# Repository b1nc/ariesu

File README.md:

# ariesu アリエス

Ariesu keyboard PCB and plate files.
A 45%ish ergo-keyboard.
Warning: This keyboard has an extremely weird layout.

----

The prototypes are in perfectly working condition.

There will not be a group-buy, however, all the PCB and case files are open-source
so feel free to order the parts yourself!

The PCB is the main part of this project, it's nothing fancy but it's something I'm
proud of. :^) (No backlits, sorry.)

Since the case files are stacked acrylic, it features a 0 degree typing angle, but
feel free to make a case for the PCB if you want something unique.

## Features (Very simple PCB) 
* Mini-B USB connection. (Yes, I know.)

* 51 keys.

* ATmega32U4

* MX-only no per key leds.

* No backlit leds.

## Thanks to
- ai03 for his PCB guide and hadi for his in-depth explanations.

- Izzy7k for sticking up with my bs and staying up with me.

- hadi's Youtube channel: https://www.youtube.com/channel/UCpWGAJr2AU7LPUwVYbBQZRg

- ai03's PCB guide: https://wiki.ai03.com/books/pcb-design/

## Addtional Items
I purchased most of the screws and standoffs from McMaster-Carr. Here are the parts
if you are going to use the stacked acrylic case in this project.

- Standoffs: Zinc-Plated Brass Female Threaded Hex Standoff 4.5mm Hex, 19mm Long, M3 x 0.5mm Thread (https://www.mcmaster.com/92080A014/)

- Screws: Brass Pan Head Slotted Screws M3 x 0.5mm Thread, 6mm Long (https://www.mcmaster.com/90928A301/)

- Bumpons: Adhesive-Back Bumpers Polyurethane, 1/2" Long, 1" Wide, 1/8" High, Durometer 65A, Black (https://www.mcmaster.com/95495K861/)

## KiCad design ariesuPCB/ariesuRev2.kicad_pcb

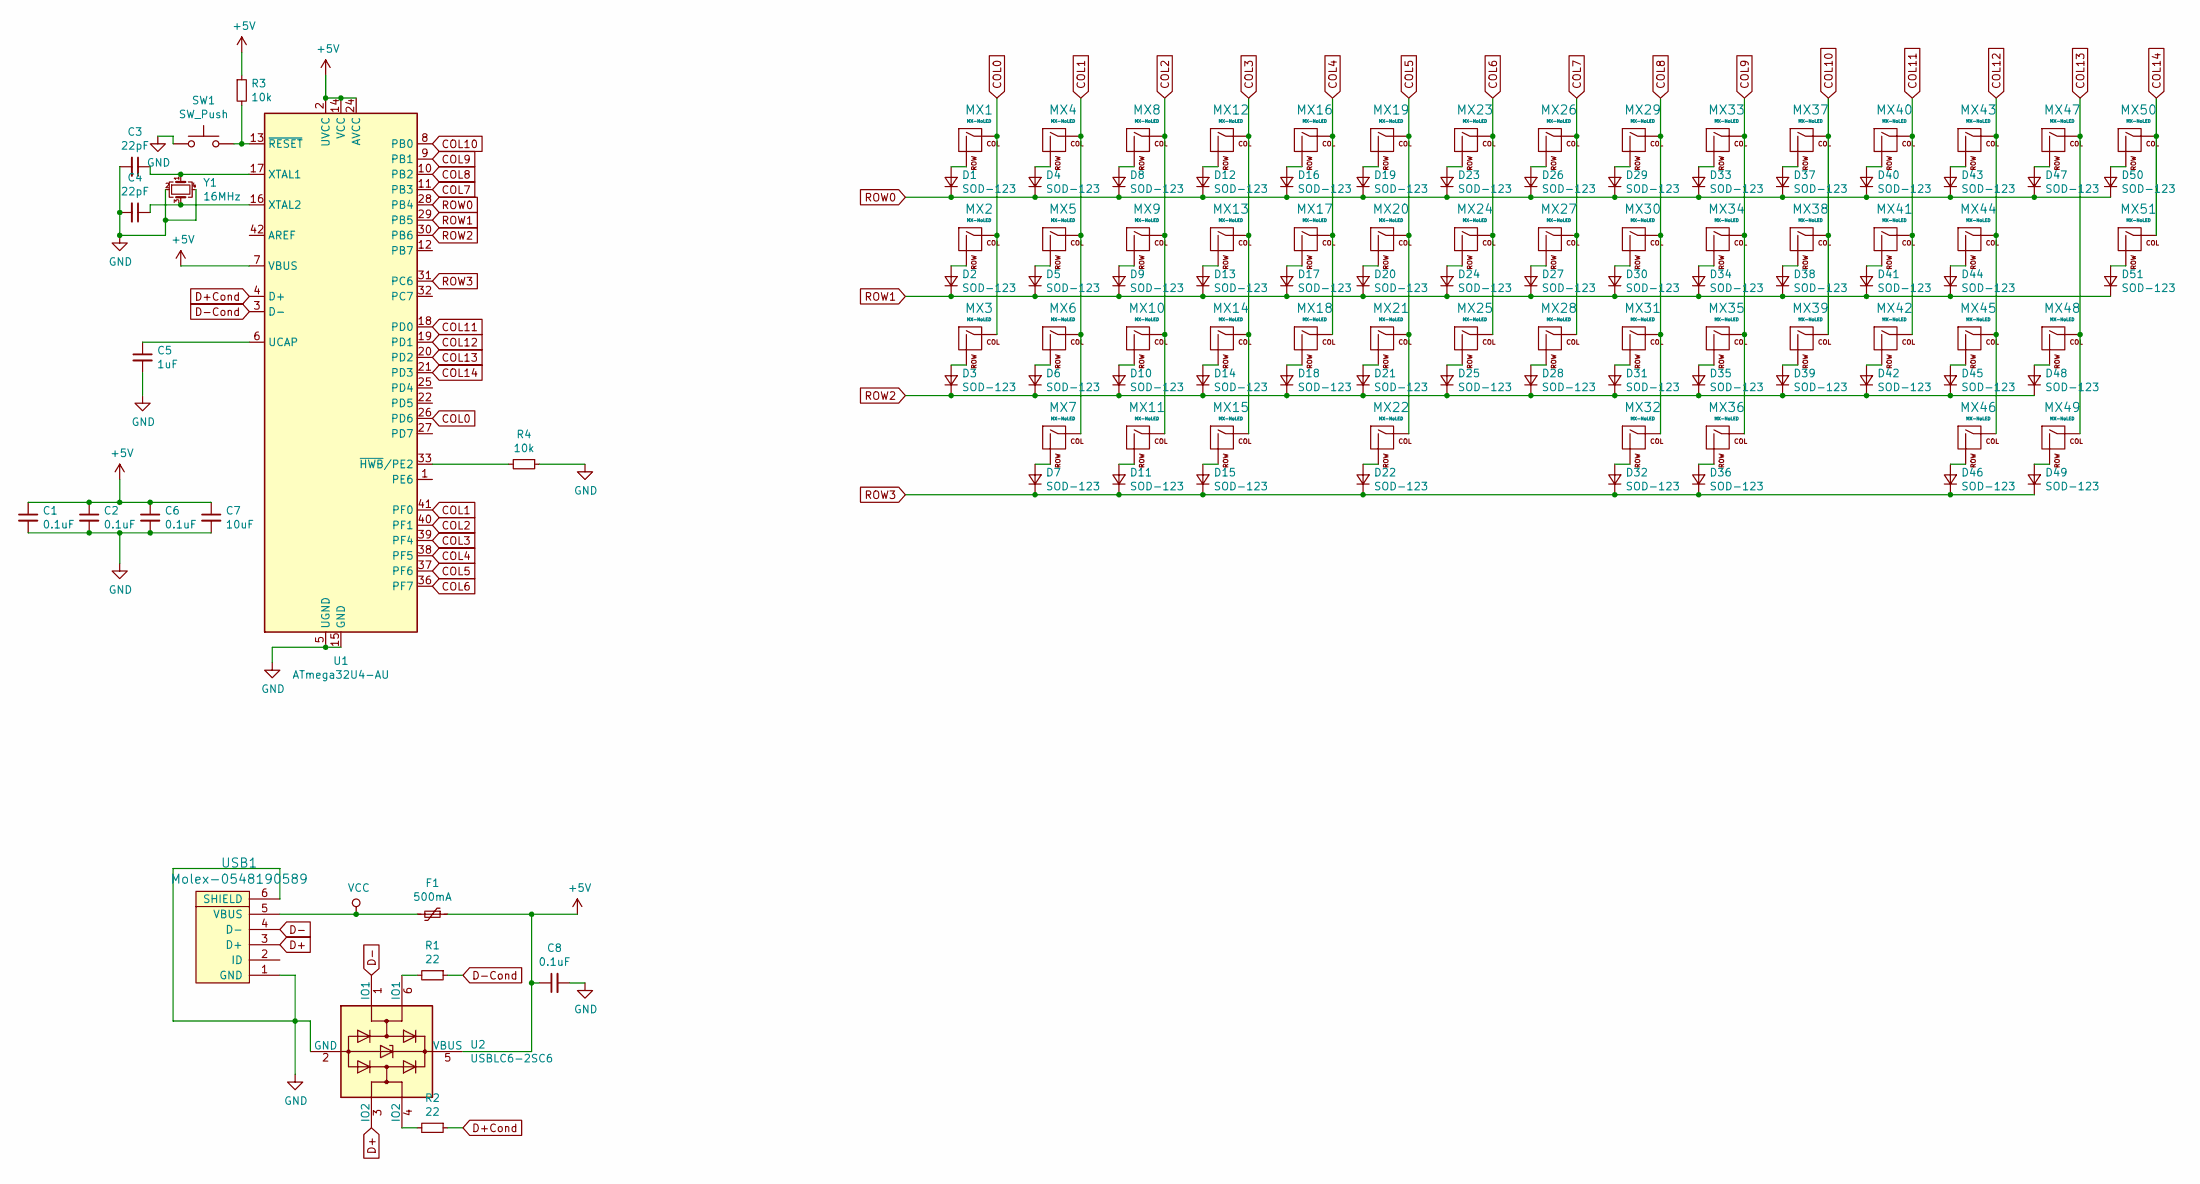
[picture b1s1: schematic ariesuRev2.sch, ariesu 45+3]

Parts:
C1, C2, C6, C8: 0.1uF; C_0805_2012Metric
C3, C4: 22pF; C_0805_2012Metric
C5: 1uF; C_0805_2012Metric
C7: 10uF; C_0805_2012Metric
D1, D2, D3, D4, D5, D6, D7, D8, D9, D10, D11, D12, D13, D14, D15, D16, D17, D18, D19, D20, D21, D22, D23, D24, D25, D26, D27, D28, D29, D30, D31, D32, D33, D34, D35, D36, D37, D38, D39, D40, D41, D42, D43, D44, D45, D46, D47, D48, D49, D50, D51: SOD-123; D_SOD-123
F1: 500mA; Fuse_1206_3216Metric
MX1, MX2, MX3, MX4, MX5, MX6, MX7, MX8, MX9, MX10, MX11, MX12, MX13, MX14, MX15, MX16, MX17, MX18, MX19, MX20, MX21, MX23, MX24, MX25, MX26, MX27, MX28, MX29, MX30, MX31, MX33, MX34, MX35, MX36, MX37, MX38, MX39, MX40, MX41, MX42, MX43, MX44, MX45, MX46, MX47, MX48, MX49, MX50, MX51: MX-NoLED; MXOnly-1U-NoLED
MX22, MX32: MX-NoLED; MXOnly-2.25U-ReversedStabilizers-NoLED
R1, R2: 22; R_0805_2012Metric
R3, R4: 10k; R_0805_2012Metric
SW1: SW_Push; SKQG-1155865
U1: ATmega32U4-AU; TQFP-44_10x10mm_P0.8mm
U2: USBLC6-2SC6; SOT-23-6
USB1: Molex-0548190589
Y1: 16MHz; Crystal_SMD_3225-4Pin_3.2x2.5mm

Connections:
+5V: C1.1, C2.1, C6.1, C7.1, C8.1, F1.1, R3.1, U1.2 (UVCC), U1.7 (VBUS), U1.14 (VCC), U1.24 (AVCC), U1.34 (VCC), U1.44 (AVCC), U2.5 (VBUS)
COL0: MX1.1 (COL), MX2.1 (COL), MX3.1 (COL), U1.26 (PD6)
COL1: MX4.1 (COL), MX5.1 (COL), MX6.1 (COL), MX7.1 (COL), U1.41 (PF0)
COL2: MX8.1 (COL), MX9.1 (COL), MX10.1 (COL), MX11.1 (COL), U1.40 (PF1)
COL3: MX12.1 (COL), MX13.1 (COL), MX14.1 (COL), MX15.1 (COL), U1.39 (PF4)
COL4: MX16.1 (COL), MX17.1 (COL), MX18.1 (COL), U1.38 (PF5)
COL5: MX19.1 (COL), MX20.1 (COL), MX21.1 (COL), MX22.1 (COL), U1.37 (PF6)
COL6: MX23.1 (COL), MX24.1 (COL), MX25.1 (COL), U1.36 (PF7)
COL7: MX26.1 (COL), MX27.1 (COL), MX28.1 (COL), U1.11 (PB3)
COL8: MX29.1 (COL), MX30.1 (COL), MX31.1 (COL), MX32.1 (COL), U1.10 (PB2)
COL9: MX33.1 (COL), MX34.1 (COL), MX35.1 (COL), MX36.1 (COL), U1.9 (PB1)
COL10: MX37.1 (COL), MX38.1 (COL), MX39.1 (COL), U1.8 (PB0)
COL11: MX40.1 (COL), MX41.1 (COL), MX42.1 (COL), U1.18 (PD0)
COL12: MX43.1 (COL), MX44.1 (COL), MX45.1 (COL), MX46.1 (COL), U1.19 (PD1)
COL13: MX47.1 (COL), MX48.1 (COL), MX49.1 (COL), U1.20 (PD2)
COL14: MX50.1 (COL), MX51.1 (COL), U1.21 (PD3)
D+: U2.3 (IO2), USB1.3 (D+)
D+Cond: R2.1, U1.4 (D+)
D-: U2.1 (IO1), USB1.4 (D-)
D-Cond: R1.1, U1.3 (D-)
GND: C1.2, C2.2, C3.2, C4.2, C5.2, C6.2, C7.2, C8.2, R4.1, SW1.1, U1.5 (UGND), U1.15 (GND), U1.23 (GND), U1.35 (GND), U1.43 (GND), U2.2 (GND), USB1.1 (GND), USB1.6 (SHIELD), Y1.2, Y1.4
unnamed: C3.1, U1.17 (XTAL1), Y1.1
unnamed: C4.1, U1.16 (XTAL2), Y1.3
unnamed: C5.1, U1.6 (UCAP)
unnamed: D1.2 (A), MX1.2 (ROW)
unnamed: D2.2 (A), MX2.2 (ROW)
unnamed: D3.2 (A), MX3.2 (ROW)
unnamed: D4.2 (A), MX4.2 (ROW)
unnamed: D5.2 (A), MX5.2 (ROW)
unnamed: D6.2 (A), MX6.2 (ROW)
unnamed: D7.2 (A), MX7.2 (ROW)
unnamed: D8.2 (A), MX8.2 (ROW)
unnamed: D9.2 (A), MX9.2 (ROW)
unnamed: D10.2 (A), MX10.2 (ROW)
unnamed: D11.2 (A), MX11.2 (ROW)
unnamed: D12.2 (A), MX12.2 (ROW)
unnamed: D13.2 (A), MX13.2 (ROW)
unnamed: D14.2 (A), MX14.2 (ROW)
unnamed: D15.2 (A), MX15.2 (ROW)
unnamed: D16.2 (A), MX16.2 (ROW)
unnamed: D17.2 (A), MX17.2 (ROW)
unnamed: D18.2 (A), MX18.2 (ROW)
unnamed: D19.2 (A), MX19.2 (ROW)
unnamed: D20.2 (A), MX20.2 (ROW)
unnamed: D21.2 (A), MX21.2 (ROW)
unnamed: D22.2 (A), MX22.2 (ROW)
unnamed: D23.2 (A), MX23.2 (ROW)
unnamed: D24.2 (A), MX24.2 (ROW)
unnamed: D25.2 (A), MX25.2 (ROW)
unnamed: D26.2 (A), MX26.2 (ROW)
unnamed: D27.2 (A), MX27.2 (ROW)
unnamed: D28.2 (A), MX28.2 (ROW)
unnamed: D29.2 (A), MX29.2 (ROW)
unnamed: D30.2 (A), MX30.2 (ROW)
unnamed: D31.2 (A), MX31.2 (ROW)
unnamed: D32.2 (A), MX32.2 (ROW)
unnamed: D33.2 (A), MX33.2 (ROW)
unnamed: D34.2 (A), MX34.2 (ROW)
unnamed: D35.2 (A), MX35.2 (ROW)
unnamed: D36.2 (A), MX36.2 (ROW)
unnamed: D37.2 (A), MX37.2 (ROW)
unnamed: D38.2 (A), MX38.2 (ROW)
unnamed: D39.2 (A), MX39.2 (ROW)
unnamed: D40.2 (A), MX40.2 (ROW)
unnamed: D41.2 (A), MX41.2 (ROW)
unnamed: D42.2 (A), MX42.2 (ROW)
unnamed: D43.2 (A), MX43.2 (ROW)
unnamed: D44.2 (A), MX44.2 (ROW)
unnamed: D45.2 (A), MX45.2 (ROW)
unnamed: D46.2 (A), MX46.2 (ROW)
unnamed: D47.2 (A), MX47.2 (ROW)
unnamed: D48.2 (A), MX48.2 (ROW)
unnamed: D49.2 (A), MX49.2 (ROW)
unnamed: D50.2 (A), MX50.2 (ROW)
unnamed: D51.2 (A), MX51.2 (ROW)
unnamed: R1.2, U2.6 (IO1)
unnamed: R2.2, U2.4 (IO2)
unnamed: R3.2, SW1.2, U1.13 (~RESET)
unnamed: R4.2, U1.33 (~HWB~/PE2)
ROW0: D1.1 (K), D4.1 (K), D8.1 (K), D12.1 (K), D16.1 (K), D19.1 (K), D23.1 (K), D26.1 (K), D29.1 (K), D33.1 (K), D37.1 (K), D40.1 (K), D43.1 (K), D47.1 (K), D50.1 (K), U1.28 (PB4)
ROW1: D2.1 (K), D5.1 (K), D9.1 (K), D13.1 (K), D17.1 (K), D20.1 (K), D24.1 (K), D27.1 (K), D30.1 (K), D34.1 (K), D38.1 (K), D41.1 (K), D44.1 (K), D51.1 (K), U1.29 (PB5)
ROW2: D3.1 (K), D6.1 (K), D10.1 (K), D14.1 (K), D18.1 (K), D21.1 (K), D25.1 (K), D28.1 (K), D31.1 (K), D35.1 (K), D39.1 (K), D42.1 (K), D45.1 (K), D48.1 (K), U1.30 (PB6)
ROW3: D7.1 (K), D11.1 (K), D15.1 (K), D22.1 (K), D32.1 (K), D36.1 (K), D46.1 (K), D49.1 (K), U1.31 (PC6)
VCC: F1.2, USB1.5 (VBUS)

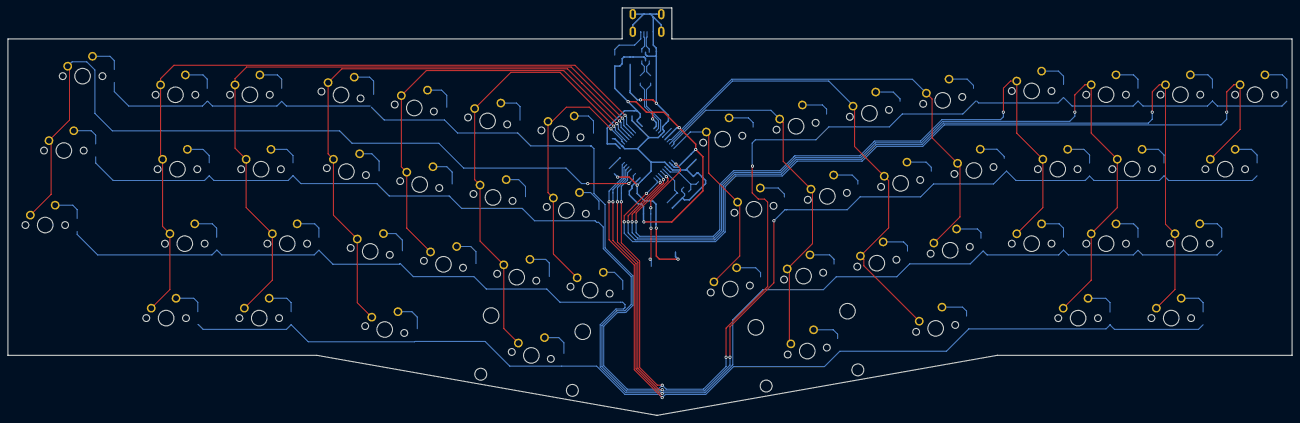
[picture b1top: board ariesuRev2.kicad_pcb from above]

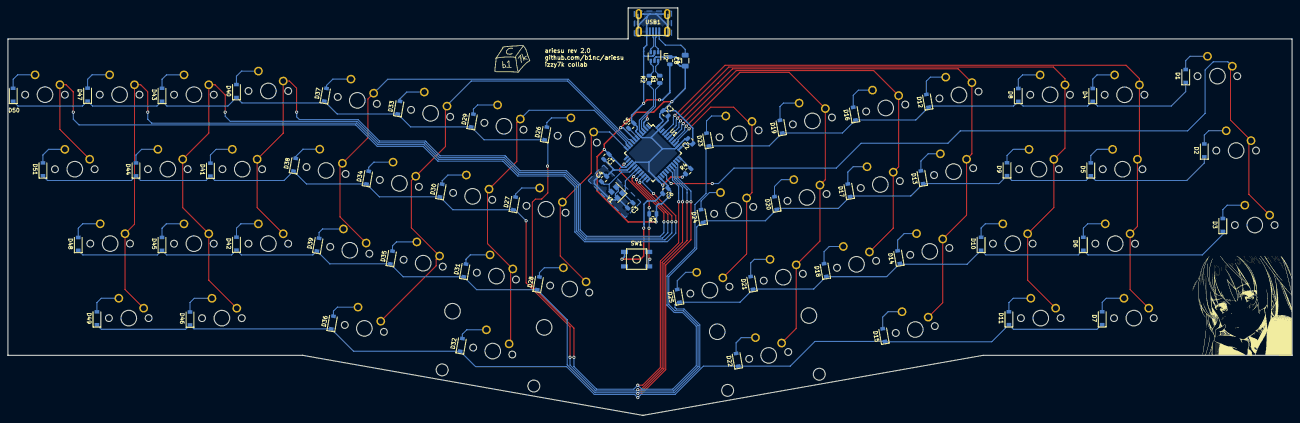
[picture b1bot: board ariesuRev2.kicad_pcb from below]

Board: 2 copper layers, 328.6 x 104.3 mm, 120 parts (69 on the bottom side), 84 nets.

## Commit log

2020-11-12 Re-formatted
2020-11-13 Updated Case Files
2020-11-16 UpdatedImages
